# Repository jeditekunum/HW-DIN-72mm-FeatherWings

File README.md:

# HW-DIN-72mm-FeatherWings
Original FeatherWings Extended for 72mm DIN Carrier

Edges stretched to 72mm.

**WARNING**

**Be aware that DIN carriers have ~2mm of unusable space around the edges. 72mm size have 68mm exposed space. The same holds true for the other dimension; the end caps also have 2mm each of unusable space. These PCBs have no extra space in that dimension. When ordering carriers they should be at least 4mm more than these PCBs. For example, the SingleWing is 22.86mm; the carrier should be at least 26.86mm.**

___

Derived from:

## Adafruit-FeatherWing-Proto-and-Doubler
PCB files for the Adafruit Proto, Doubler and Tripler FeatherWings PCB files

Format is EagleCAD schematic and board layout

For more details, check out the product pages at

  * https://www.adafruit.com/product/2884
  * https://www.adafruit.com/product/2890
  * https://www.adafruit.com/products/3417

Adafruit invests time and resources providing this open source design, 
please support Adafruit and open-source hardware by purchasing 
products from Adafruit!

Designed by Adafruit Industries.  
Creative Commons Attribution, Share-Alike license, check license.txt for more information
All text above must be included in any redistribution

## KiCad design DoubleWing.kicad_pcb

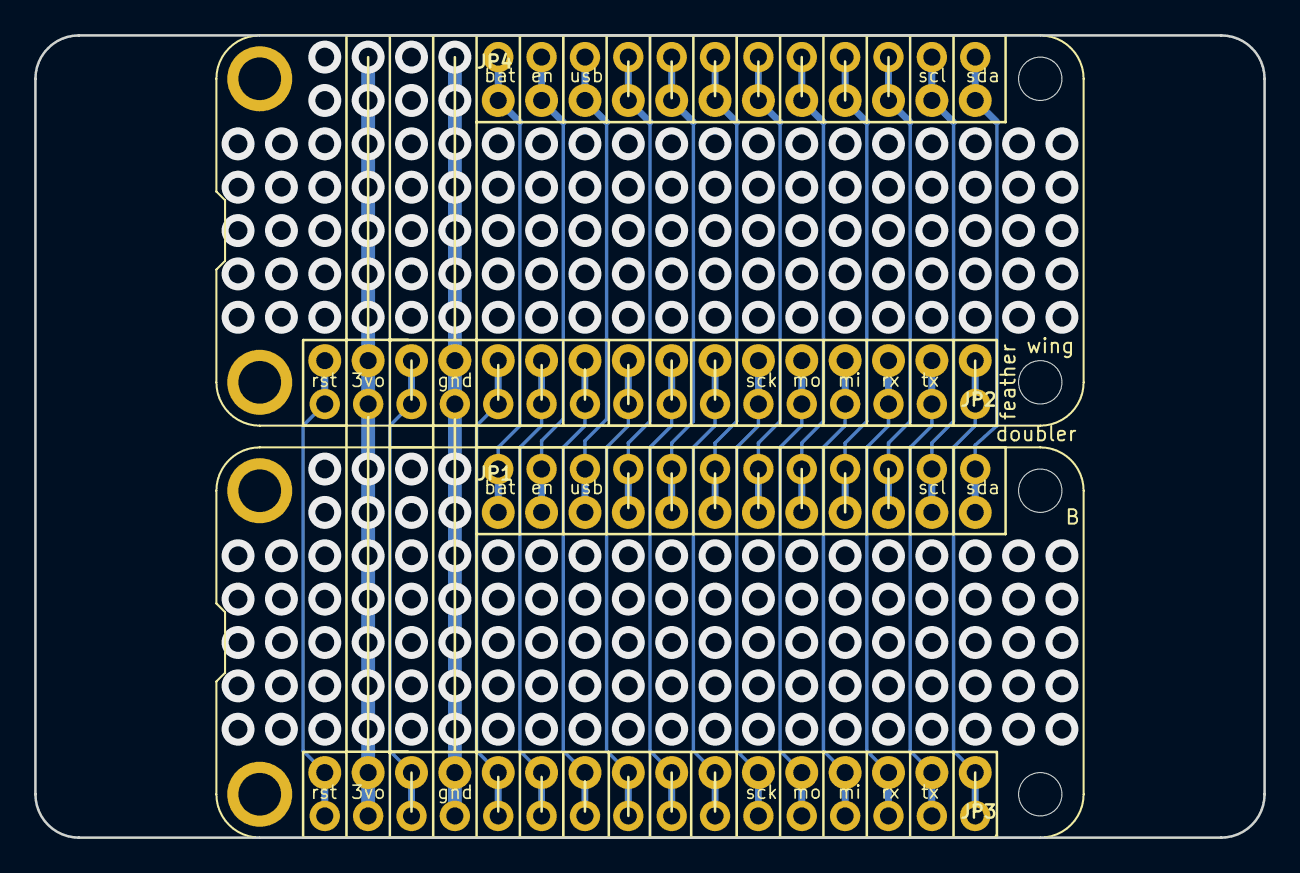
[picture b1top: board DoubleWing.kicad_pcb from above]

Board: 2 copper layers, 72.0 x 47.0 mm, 6 parts (0 on the bottom side), 28 nets.

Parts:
JP1, JP4: HEADER-1X1276MIL; 1X12_ROUND_76MIL
JP2, JP3: HEADER-1X16_76MIL; 1X16_ROUND_76MIL
MS1, MS2: FEATHERWING_NODIM; FEATHERWING_DIM

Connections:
unnamed: JP1.1, JP4.1, MS1.28, MS2.28
unnamed: JP1.2, JP4.2, MS1.27, MS2.27
unnamed: JP1.3, JP4.3, MS1.26, MS2.26
unnamed: JP1.4, JP4.4, MS1.25, MS2.25
unnamed: JP1.5, JP4.5, MS1.24, MS2.24
unnamed: JP1.6, JP4.6, MS1.23, MS2.23
unnamed: JP1.7, JP4.7, MS1.22, MS2.22
unnamed: JP1.8, JP4.8, MS1.21, MS2.21
unnamed: JP1.9, JP4.9, MS1.20, MS2.20
unnamed: JP1.10, JP4.10, MS1.19, MS2.19
unnamed: JP1.11, JP4.11, MS1.18, MS2.18
unnamed: JP1.12, JP4.12, MS1.17, MS2.17
unnamed: JP2.1, JP3.1, MS1.16, MS2.16
unnamed: JP2.2, JP3.2, MS1.15, MS2.15
unnamed: JP2.3, JP3.3, MS1.14, MS2.14
unnamed: JP2.4, JP3.4, MS1.13, MS2.13
unnamed: JP2.5, JP3.5, MS1.12, MS2.12
unnamed: JP2.6, JP3.6, MS1.11, MS2.11
unnamed: JP2.7, JP3.7, MS1.10, MS2.10
unnamed: JP2.8, JP3.8, MS1.9, MS2.9
unnamed: JP2.9, JP3.9, MS1.8, MS2.8
unnamed: JP2.10, JP3.10, MS1.7, MS2.7
unnamed: JP2.11, JP3.11, MS1.6, MS2.6
unnamed: JP2.12, JP3.12, MS1.5, MS2.5
unnamed: JP2.13, JP3.13, MS1.4, MS2.4
unnamed: JP2.14, JP3.14, MS1.3, MS2.3
unnamed: JP2.15, JP3.15, MS1.2, MS2.2
unnamed: JP2.16, JP3.16, MS1.1, MS2.1

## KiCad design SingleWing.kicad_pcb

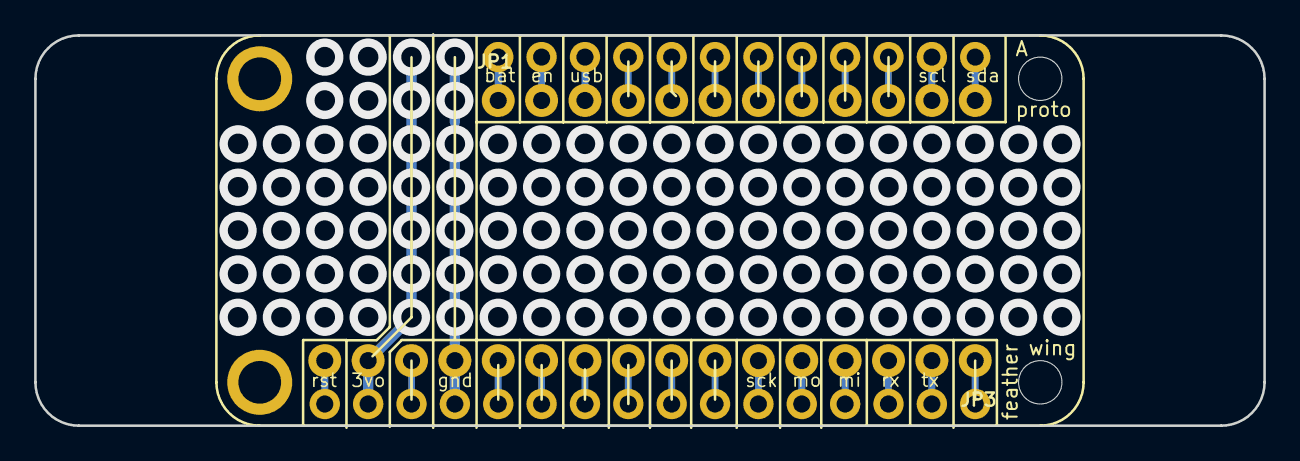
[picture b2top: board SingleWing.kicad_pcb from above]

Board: 2 copper layers, 72.0 x 22.9 mm, 3 parts (0 on the bottom side), 28 nets.

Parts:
JP1: HEADER-1X1276MIL; 1X12_ROUND_76MIL
JP3: HEADER-1X16_76MIL; 1X16_ROUND_76MIL
MS1: FEATHERWING

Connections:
unnamed: JP1.1, MS1.28
unnamed: JP1.2, MS1.27
unnamed: JP1.3, MS1.26
unnamed: JP1.4, MS1.25
unnamed: JP1.5, MS1.24
unnamed: JP1.6, MS1.23
unnamed: JP1.7, MS1.22
unnamed: JP1.8, MS1.21
unnamed: JP1.9, MS1.20
unnamed: JP1.10, MS1.19
unnamed: JP1.11, MS1.18
unnamed: JP1.12, MS1.17
unnamed: JP3.1, MS1.16
unnamed: JP3.2, MS1.15
unnamed: JP3.3, MS1.14
unnamed: JP3.4, MS1.13
unnamed: JP3.5, MS1.12
unnamed: JP3.6, MS1.11
unnamed: JP3.7, MS1.10
unnamed: JP3.8, MS1.9
unnamed: JP3.9, MS1.8
unnamed: JP3.10, MS1.7
unnamed: JP3.11, MS1.6
unnamed: JP3.12, MS1.5
unnamed: JP3.13, MS1.4
unnamed: JP3.14, MS1.3
unnamed: JP3.15, MS1.2
unnamed: JP3.16, MS1.1

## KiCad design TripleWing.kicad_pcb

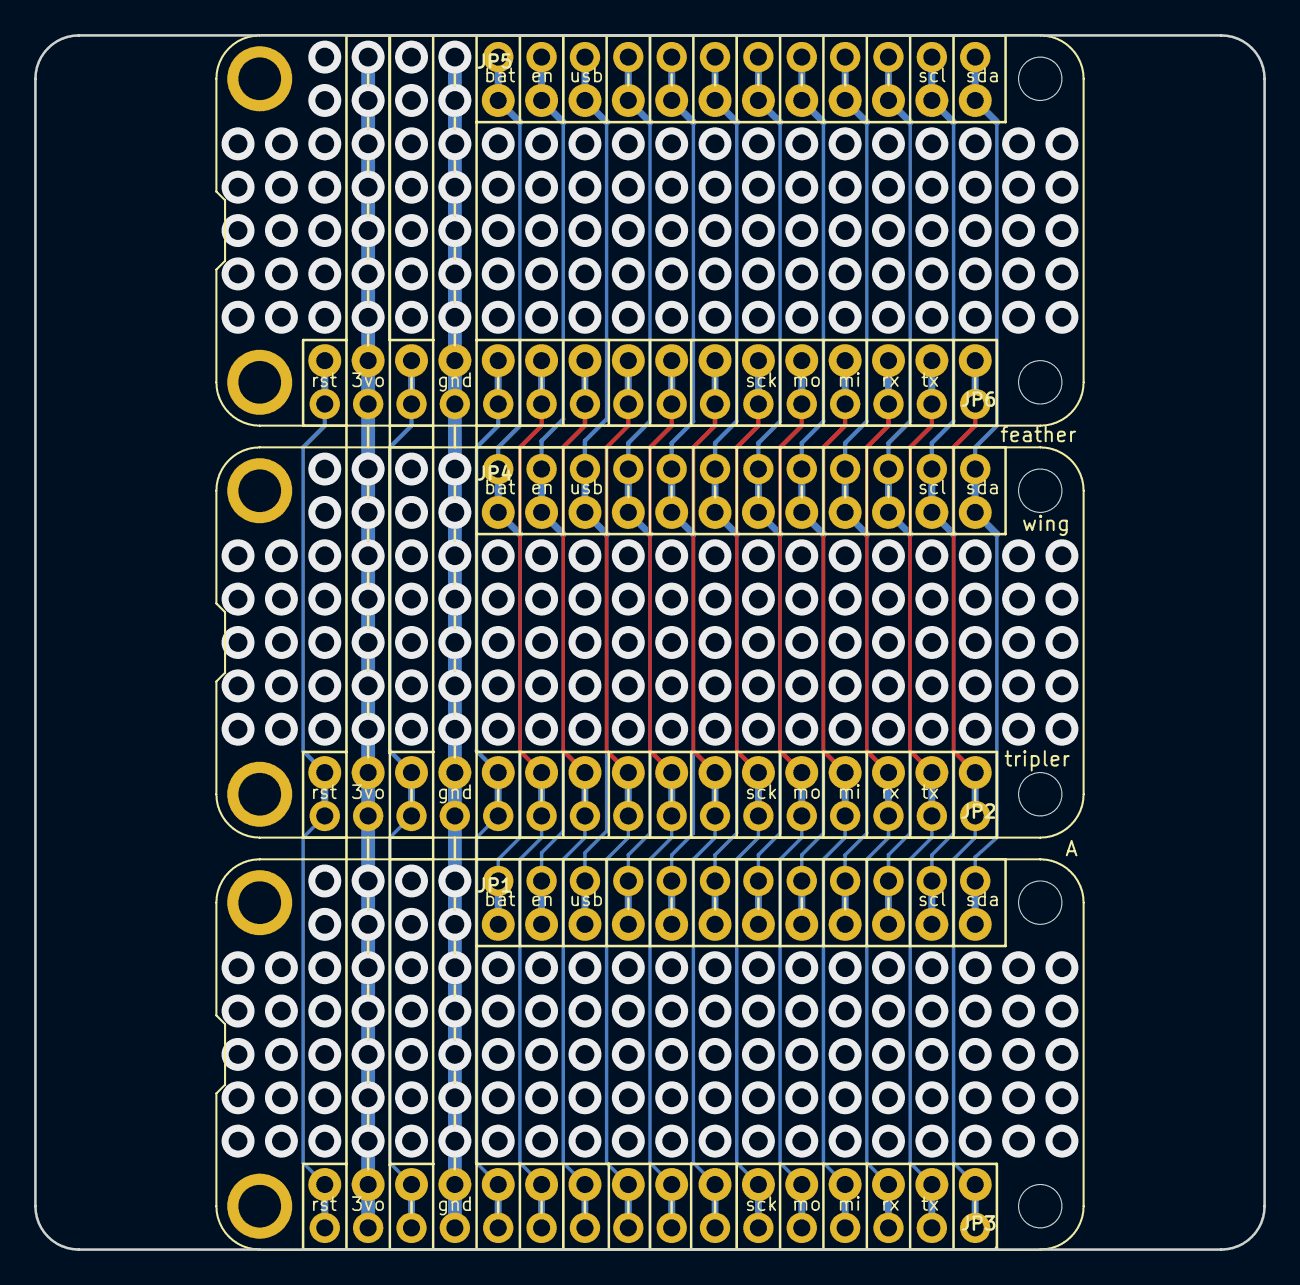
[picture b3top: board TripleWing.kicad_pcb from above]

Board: 2 copper layers, 72.0 x 71.1 mm, 9 parts (0 on the bottom side), 28 nets.

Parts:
JP1, JP4, JP5: HEADER-1X1276MIL; 1X12_ROUND_76MIL
JP2, JP3, JP6: HEADER-1X16_76MIL; 1X16_ROUND_76MIL
MS1, MS2, MS3: FEATHERWING_NODIM; FEATHERWING_DIM

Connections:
unnamed: JP1.1, JP4.1, JP5.1, MS1.28, MS2.28, MS3.28
unnamed: JP1.2, JP4.2, JP5.2, MS1.27, MS2.27, MS3.27
unnamed: JP1.3, JP4.3, JP5.3, MS1.26, MS2.26, MS3.26
unnamed: JP1.4, JP4.4, JP5.4, MS1.25, MS2.25, MS3.25
unnamed: JP1.5, JP4.5, JP5.5, MS1.24, MS2.24, MS3.24
unnamed: JP1.6, JP4.6, JP5.6, MS1.23, MS2.23, MS3.23
unnamed: JP1.7, JP4.7, JP5.7, MS1.22, MS2.22, MS3.22
unnamed: JP1.8, JP4.8, JP5.8, MS1.21, MS2.21, MS3.21
unnamed: JP1.9, JP4.9, JP5.9, MS1.20, MS2.20, MS3.20
unnamed: JP1.10, JP4.10, JP5.10, MS1.19, MS2.19, MS3.19
unnamed: JP1.11, JP4.11, JP5.11, MS1.18, MS2.18, MS3.18
unnamed: JP1.12, JP4.12, JP5.12, MS1.17, MS2.17, MS3.17
unnamed: JP2.1, JP3.1, JP6.1, MS1.16, MS2.16, MS3.16
unnamed: JP2.2, JP3.2, JP6.2, MS1.15, MS2.15, MS3.15
unnamed: JP2.3, JP3.3, JP6.3, MS1.14, MS2.14, MS3.14
unnamed: JP2.4, JP3.4, JP6.4, MS1.13, MS2.13, MS3.13
unnamed: JP2.5, JP3.5, JP6.5, MS1.12, MS2.12, MS3.12
unnamed: JP2.6, JP3.6, JP6.6, MS1.11, MS2.11, MS3.11
unnamed: JP2.7, JP3.7, JP6.7, MS1.10, MS2.10, MS3.10
unnamed: JP2.8, JP3.8, JP6.8, MS1.9, MS2.9, MS3.9
unnamed: JP2.9, JP3.9, JP6.9, MS1.8, MS2.8, MS3.8
unnamed: JP2.10, JP3.10, JP6.10, MS1.7, MS2.7, MS3.7
unnamed: JP2.11, JP3.11, JP6.11, MS1.6, MS2.6, MS3.6
unnamed: JP2.12, JP3.12, JP6.12, MS1.5, MS2.5, MS3.5
unnamed: JP2.13, JP3.13, JP6.13, MS1.4, MS2.4, MS3.4
unnamed: JP2.14, JP3.14, JP6.14, MS1.3, MS2.3, MS3.3
unnamed: JP2.15, JP3.15, JP6.15, MS1.2, MS2.2, MS3.2
unnamed: JP2.16, JP3.16, JP6.16, MS1.1, MS2.1, MS3.1

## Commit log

2019-07-18 Single, Double, and Triple AdaFruit FeatherWings extended to 72mm for DIN carriers.
